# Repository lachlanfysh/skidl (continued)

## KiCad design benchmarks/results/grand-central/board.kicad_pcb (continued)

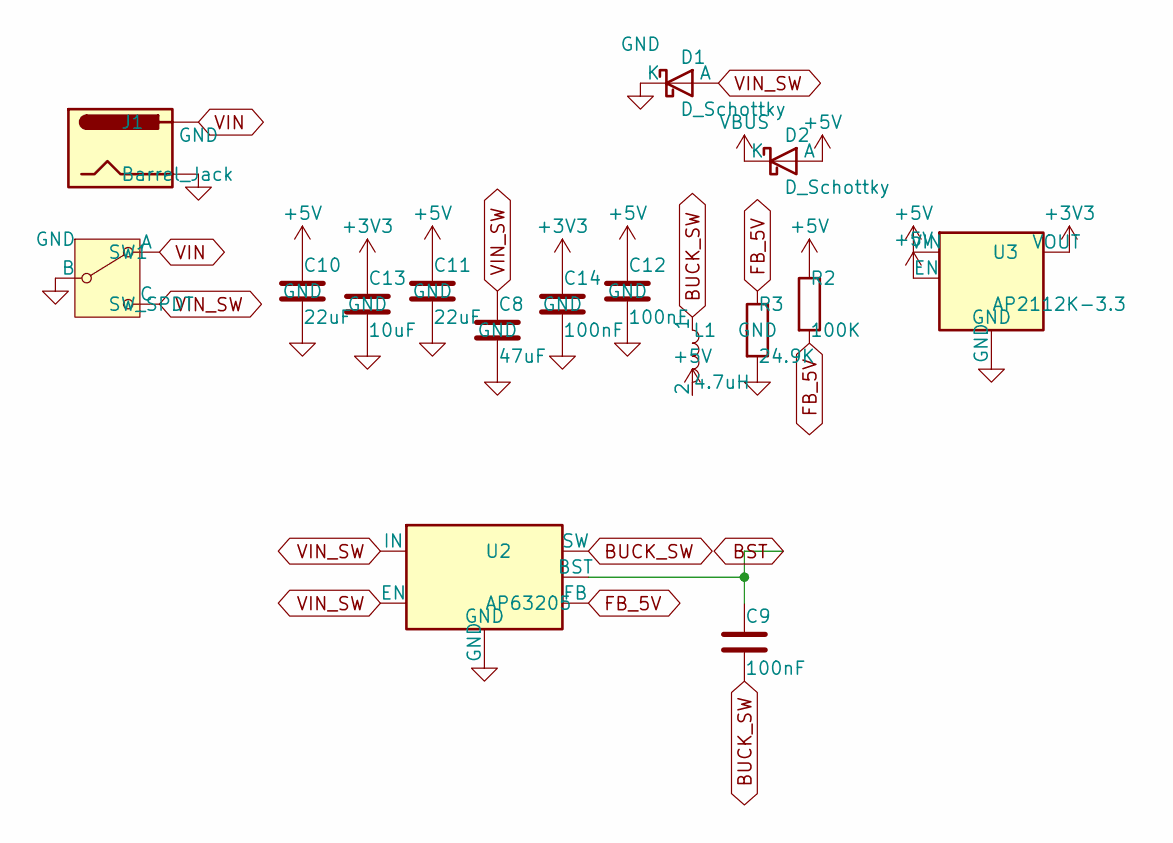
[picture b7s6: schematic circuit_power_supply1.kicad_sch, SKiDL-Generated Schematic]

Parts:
C8: 47uF; C_0805_2012Metric
C9, C12, C14: 100nF; C_0603_1608Metric
C10, C11: 22uF; C_0805_2012Metric
C13: 10uF; C_0805_2012Metric
D1, D2: D_Schottky; D_SMA
J1: Barrel_Jack; BarrelJack_CUI_PJ-063AH_Horizontal
L1: 4.7uH; L_0805_2012Metric
R2: 100K; R_0603_1608Metric
R3: 24.9K; R_0603_1608Metric
SW1: SW_SPDT; SW_DIP_SPSTx01_Slide_6.7x4.1mm_W8.61mm_P2.54mm_LowProfile
U2: AP63205; SOT-23-6
U3: AP2112K-3.3; SOT-23-5

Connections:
+3V3: C13.1, C14.1, U3.5 (VOUT); also elsewhere on the board
+5V: C10.1, C11.1, C12.1, D2.2 (A), L1.2, R2.1, U3.1 (VIN), U3.3 (EN); also elsewhere on the board
BST: C9.1, U2.6 (BST)
BUCK_SW: C9.2, L1.1, U2.5 (SW)
FB_5V: R2.2, R3.1, U2.1 (FB)
GND: C8.2, C10.2, C11.2, C12.2, C13.2, C14.2, D1.1 (K), J1.2, R3.2, SW1.2 (B), U2.4 (GND), U3.2 (GND); also elsewhere on the board
VBUS: D2.1 (K); also elsewhere on the board
VIN: J1.1, SW1.1 (A); also elsewhere on the board
VIN_SW: C8.1, D1.2 (A), SW1.3 (C), U2.2 (EN), U2.3 (IN)

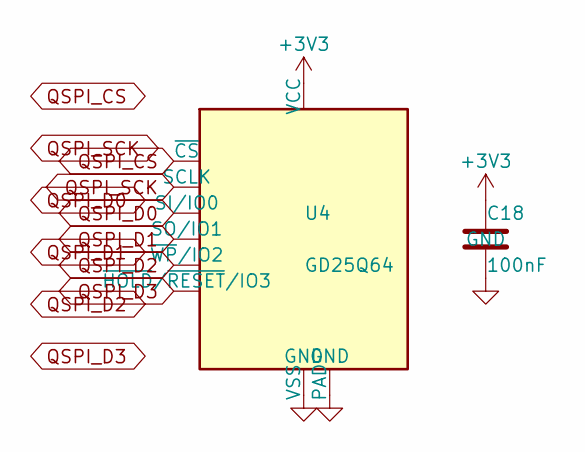
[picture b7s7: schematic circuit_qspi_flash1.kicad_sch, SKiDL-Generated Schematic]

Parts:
C18: 100nF; C_0603_1608Metric
U4: GD25Q64; SOIC-8_3.9x4.9mm_P1.27mm

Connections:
+3V3: C18.1, U4.8 (VCC); also elsewhere on the board
GND: C18.2, U4.4 (VSS), U4.9 (PAD); also elsewhere on the board
QSPI_CS: U4.1 (~CS); also elsewhere on the board
QSPI_D0: U4.5 (SI/IO0); also elsewhere on the board
QSPI_D1: U4.2 (SO/IO1); also elsewhere on the board
QSPI_D2: U4.3 (~WP/IO2); also elsewhere on the board
QSPI_D3: U4.7 (~HOLD/~RESET/IO3); also elsewhere on the board
QSPI_SCK: U4.6 (SCLK); also elsewhere on the board

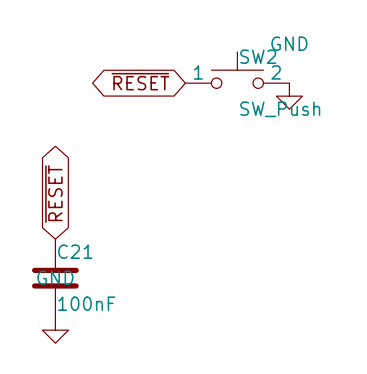
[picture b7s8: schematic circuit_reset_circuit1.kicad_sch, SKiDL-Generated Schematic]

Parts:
C21: 100nF; C_0603_1608Metric
SW2: SW_Push; SW_DIP_SPSTx01_Slide_6.7x4.1mm_W8.61mm_P2.54mm_LowProfile

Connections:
GND: C21.2, SW2.2; also elsewhere on the board
~RESET: C21.1, SW2.1; also elsewhere on the board

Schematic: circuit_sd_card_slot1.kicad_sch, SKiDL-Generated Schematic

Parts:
C19: 100nF; C_0603_1608Metric
J3: Micro_SD_Card; microSD_HC_Hirose_DM3AT-SF-PEJM5
R4, R5: 10K; R_0603_1608Metric

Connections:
+3V3: C19.1, J3.4 (VDD), R4.1, R5.1; also elsewhere on the board
GND: C19.2, J3.6 (VSS), J3.9 (SHIELD); also elsewhere on the board
SD_CS: J3.2 (DAT3/CD); also elsewhere on the board
SD_DAT1: J3.8 (DAT1), R4.2
SD_DAT2: J3.1 (DAT2), R5.2
SD_MISO: J3.7 (DAT0); also elsewhere on the board
SD_MOSI: J3.3 (CMD); also elsewhere on the board
SD_SCK: J3.5 (CLK); also elsewhere on the board

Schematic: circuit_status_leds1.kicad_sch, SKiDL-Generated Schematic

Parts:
D5, D6: LED; LED_0603_1608Metric
R6, R7: 1K; R_0603_1608Metric

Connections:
+3V3: D5.1 (K); also elsewhere on the board
GND: R6.2, R7.2; also elsewhere on the board
GPIO13: D6.1 (K); also elsewhere on the board
unnamed: D5.2 (A), R6.1
unnamed: D6.2 (A), R7.1

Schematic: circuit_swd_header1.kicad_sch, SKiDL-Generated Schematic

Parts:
J4: Conn_02x05_Odd_Even; PinHeader_2x05_P1.27mm_Vertical

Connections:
+3V3: J4.1; also elsewhere on the board
GND: J4.3, J4.5, J4.6, J4.7, J4.8, J4.9; also elsewhere on the board
SWDCLK: J4.4; also elsewhere on the board
SWDIO: J4.2; also elsewhere on the board
~RESET: J4.10; also elsewhere on the board

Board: 2 copper layers, 53 parts (0 on the bottom side), 63 nets, no tracks yet.

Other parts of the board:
C15: 100nF; C_0603_1608Metric
D3: D_TVS; D_SMA
J2: USB_B_Micro; USB_Micro-B_Molex-105017-0001

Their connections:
GND: C15.2, D3.2, J2.5, J2.6; also elsewhere on the board
USB_DM: J2.2; also elsewhere on the board
USB_DP: D3.1, J2.3; also elsewhere on the board
VBUS: C15.1, J2.1; also elsewhere on the board

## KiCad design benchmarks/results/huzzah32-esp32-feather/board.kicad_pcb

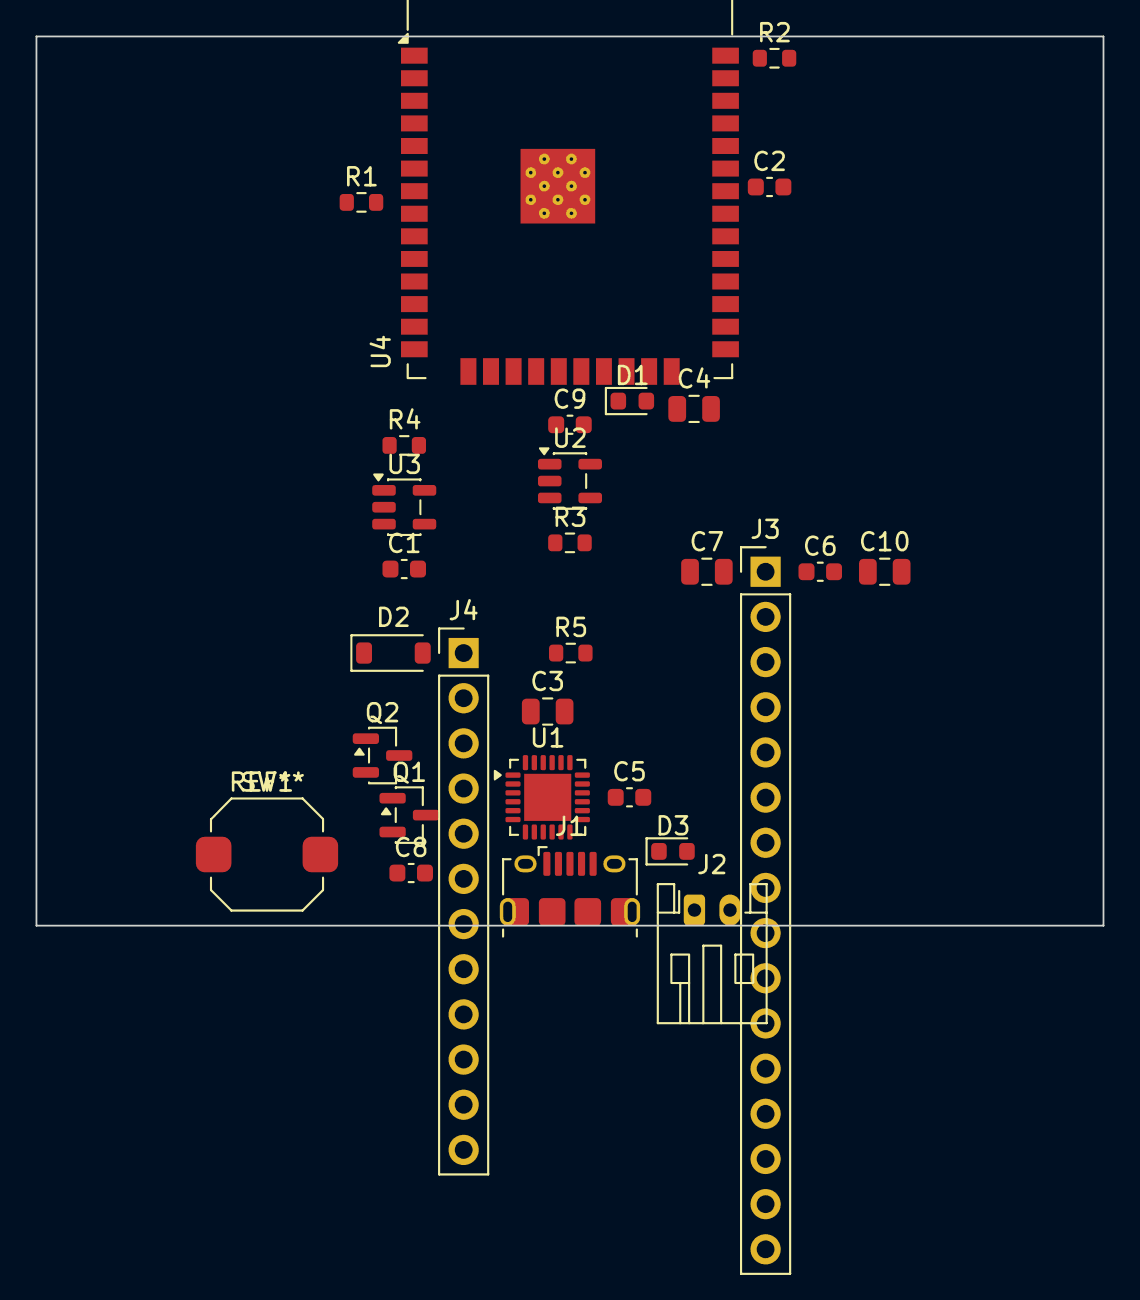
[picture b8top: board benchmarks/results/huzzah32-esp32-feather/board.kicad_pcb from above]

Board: 2 copper layers, 60.0 x 50.0 mm, 29 parts (0 on the bottom side), 35 nets, no tracks yet.

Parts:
C1, C2, C5, C6, C8, C9: 100nF; C_0603_1608Metric
C3, C4: 4.7uF; C_0805_2012Metric
C7, C10: 10uF; C_0805_2012Metric
D1: ORANGE; LED_0603_1608Metric
D2: MBR120; D_SOD-123
D3: RED; LED_0603_1608Metric
J1: USB_B_Micro; USB_Micro-B_Amphenol_10118194_Horizontal
J2: Conn_01x02; JST_PH_S2B-PH-K_1x02_P2.00mm_Horizontal
J3: Conn_01x16; PinHeader_1x16_P2.54mm_Vertical
J4: Conn_01x12; PinHeader_1x12_P2.54mm_Vertical
Q1, Q2: Q_NPN; SOT-23
R1, R2: 10K; R_0603_1608Metric
R3: 2K; R_0603_1608Metric
R4, R5: 1K; R_0603_1608Metric
SW1: SW_Push; SW_Push_1TS009xxxx-xxxx-xxxx_6x6x5mm
U1: CP2104; QFN-24-1EP_4x4mm_P0.5mm_EP2.65x2.65mm
U2: MCP73831-2-OT; SOT-23-5
U3: AP2112K-3.3; SOT-23-5
U4: ESP32-WROOM-32

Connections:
+3V3: C2.1, C6.1, C7.1, C9.1, C10.1, J3.2, R1.1, R2.1, U1.5, U3.5, U4.2
CHG_STAT: D1.1, U2.1
EN: C8.1, J3.1, J4.2, R1.2, SW1.1, U4.3
GND: C1.2, C2.2, C3.2, C4.2, C5.2, C6.2, C7.2, C8.2, C9.2, C10.2, D3.1, J1.5, J1.6, J2.2, J3.4, R3.2, SW1.2, U1.2, U1.25, U2.2, U3.2, U4.1, U4.15, U4.38, U4.39
IO0: R2.2, U4.25
IO4: J3.10, U4.26
IO5: J3.11, U4.29
IO12: J4.5, U4.14
IO13: J4.4, R5.1, U4.16
IO14: J4.10, U4.13
IO15: J4.8, U4.23
IO16: J3.14, U4.27
IO17: J3.15, U4.28
IO18: J3.12, U4.30
IO19: J3.13, U4.31
IO21: J3.16, U4.33
IO22: J4.11, U4.36
IO23: J4.12, U4.37
IO25: J3.6, U4.10
IO26: J3.5, U4.11
IO27: J4.6, U4.12
IO32: J4.9, U4.8
IO33: J4.7, U4.9
IO34: J3.7, U4.6
unnamed: D1.2, R4.2
unnamed: D3.2, R5.2
PROG: R3.1, U2.5
RXD0: U1.21, U4.34
SENSOR_VN: J3.8, U4.5
SENSOR_VP: J3.9, U4.4
TXD0: U1.20, U4.35
USB_D+: J1.3, U1.3
USB_D-: J1.2, U1.4
VBAT: C4.1, D2.2, J2.1, J4.1, U2.3
VBUS: C1.1, C3.1, C5.1, D2.1, J1.1, J4.3, R4.1, U1.6, U1.7, U2.4, U3.1, U3.3

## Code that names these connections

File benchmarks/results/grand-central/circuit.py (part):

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              qspi_sck, qspi_cs, qspi_d0, qspi_d1, qspi_d2, qspi_d3,
              sd_sck, sd_mosi, sd_miso, sd_cs,
              neopixel_data, i2s_sck, i2s_ws, i2s_sd,
              swdio, swdclk, aref, dac0_out, dac1_out, vddcore, gpio):
    """ATSAMD51J20A in 64-pin TQFP with decoupling and crystals."""

    mcu = Part("MCU_Microchip_SAMD", "ATSAMD51J20A-A", value="ATSAMD51J20A",
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    c_vcore[1] += vddcore
    c_vcore[2] += gnd

    # USB (PA24=D-, PA25=D+)
    mcu["PA24"] += usb_dm
    mcu["PA25"] += usb_dp

    # Reset with pull-up
    mcu["~{RESET}"] += reset_n
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    r_rst[1] += v3v3
    r_rst[2] += reset_n

    # SWD (PA30=SWCLK, PA31=SWDIO)
    mcu["PA30"] += swdclk
    mcu["PA31"] += swdio

    # AREF (VDDANA pin provides analog reference, PA03 is VREFA)
    mcu["PA03"] += aref

    # QSPI flash connections (PA08-PA11 = D0-D3, PB10=SCK, PB11=CS)
    mcu["PA08"] += qspi_d0
    mcu["PA09"] += qspi_d1
    mcu["PA10"] += qspi_d2
    mcu["PA11"] += qspi_d3
    mcu["PB10"] += qspi_sck
    mcu["PB11"] += qspi_cs

    # SD card SPI (using SERCOM on PB12-PB15)
    mcu["PB12"] += sd_mosi
    mcu["PB13"] += sd_sck
    mcu["PB14"] += sd_miso
    mcu["PB15"] += sd_cs

    # NeoPixel (PB22)
    mcu["PB22"] += neopixel_data

    # I2S (PB16=SCK, PB17=WS, PA22=SD)
    mcu["PB16"] += i2s_sck
    mcu["PB17"] += i2s_ws
    mcu["PA22"] += i2s_sd

    # DAC outputs (PA02=DAC0, PA05=DAC1)
    mcu["PA02"] += dac0_out
    mcu["PA05"] += dac1_out

    # GPIO pin assignments to headers
    gpio_map = {
        "PA00": 0, "PA01": 1,
        "PA04": 2, "PA06": 3, "PA07": 4,
        "PA12": 5, "PA13": 6, "PA14": 7, "PA15": 8,
        "PA16": 9, "PA17": 10, "PA18": 11, "PA19": 12,
        "PA20": 13, "PA21": 14, "PA23": 15, "PA27": 16,
        "PB00": 17, "PB01": 18, "PB02": 19, "PB03": 20,
        "PB04": 21, "PB05": 22, "PB06": 23, "PB07": 24,
        "PB08": 25, "PB09": 26,
        "PB23": 27, "PB30": 28, "PB31": 29,
    }
    for pin_name, gpio_idx in gpio_map.items():
        mcu[pin_name] += gpio[gpio_idx]
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@subcircuit
def crystal_oscillators(v3v3, gnd, gpio):
    """12MHz main crystal and 32.768kHz RTC crystal.
    Connected to PA00/PA01 (XIN/XOUT) for main and PB**/PB** for 32k."""

    # Note: SAMD51 J variant has no dedicated XOSC pins.
    # Main clock typically uses internal DFLL48M with USB SOF reference.
    # 32.768kHz crystal on PA00 (XIN32) / PA01 (XOUT32) for RTC.
    y_rtc = Part("Device", "Crystal", value="32.768kHz",
                 footprint="Crystal:Crystal_SMD_2012-2Pin_2.0x1.2mm")
    xin32 = gpio[0]    # PA00 = XIN32
    xout32 = gpio[1]   # PA01 = XOUT32
    y_rtc[1] += xin32
    y_rtc[2] += xout32

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    j_swd[1] += v3v3       # Pin 1: VTref
    j_swd[2] += swdio      # Pin 2: SWDIO
    j_swd[3] += gnd        # Pin 3: GND
    j_swd[4] += swdclk     # Pin 4: SWDCLK
    j_swd[5] += gnd        # Pin 5: GND
    j_swd[6] += gnd
    j_swd[7] += gnd
    j_swd[8] += gnd
    j_swd[9] += gnd
    j_swd[10] += reset_n   # Pin 10: nRESET


# ============================================================
# Subcircuit: Arduino Headers
# ============================================================
@subcircuit
def arduino_headers(v5v, v3v3, gnd, gpio, aref, dac0_out, dac1_out, reset_n, vin_raw):
    """Arduino Mega form factor pin headers."""

    # Digital header 1 (1x16): D0-D13, GND, AREF
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    # ICSP/SPI header (2x3)
    j_icsp = Part("Connector_Generic", "Conn_02x03_Odd_Even",
                  footprint="Connector_PinHeader_2.54mm:PinHeader_2x03_P2.54mm_Vertical")
    j_icsp[1] += gpio[26]   # MISO (PB09)
    j_icsp[2] += v5v
    j_icsp[3] += gpio[25]   # SCK (PB08)
    j_icsp[4] += gpio[24]   # MOSI (PB07)
    j_icsp[5] += reset_n
    j_icsp[6] += gnd

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# ============================================================
@subcircuit
def status_leds(v3v3, gnd, gpio):
    """Power LED + user LED (on GPIO13 / D13)."""

    # Power LED (green)
    led_pwr = Part("Device", "LED",
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          qspi_sck, qspi_cs, qspi_d0, qspi_d1, qspi_d2, qspi_d3,
          sd_sck, sd_mosi, sd_miso, sd_cs,
          neopixel_data, i2s_sck, i2s_ws, i2s_sd,
          swdio, swdclk, aref, dac0_out, dac1_out, vddcore, gpio)

power_supply(vin_raw, vin_switched, v5v, v3v3, vbus, gnd)

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
swd_header(v3v3, gnd, swdio, swdclk, reset_n)

arduino_headers(v5v, v3v3, gnd, gpio, aref, dac0_out, dac1_out, reset_n, vin_raw)

status_leds(v3v3, gnd, gpio)

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
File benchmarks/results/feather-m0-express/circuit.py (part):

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ATSAMD21G18A ARM Cortex M0+ 48MHz, 3.3V.
256KB flash, 32KB RAM. USB bootloader (UF2).
2MB SPI flash (GD25Q16) for CircuitPython.
NeoPixel WS2812B on PA06. MCP73831 LiPo charger.
AP2112K-3.3 LDO. Schottky diode USB/battery OR.
Feather form factor ~51x23mm, 2x 1x16 + 1x12 headers.
"""
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                 footprint="Capacitor_SMD:C_0603_1608Metric", ref="C_MCU" + str(i+1))
        v3v3 += c[1]; gnd += c[2]

    # USB D+/D- (PA24=D-, PA25=D+)
    mcu["PA24"] += usb_dm
    mcu["PA25"] += usb_dp

    # 32.768kHz crystal PA00/PA01
    mcu["PA00"] += xin
    mcu["PA01"] += xout

    # Reset (pin 40 = ~{RESET} — use pin number for reliability)
    mcu[40] += reset_n

    # SWD: PA30=SWCLK, PA31=SWDIO
    mcu["PA30"] += swclk
    mcu["PA31"] += swdio

    # I2C SERCOM3: PA22=SDA, PA23=SCL
    mcu["PA22"] += sda
    mcu["PA23"] += scl

    # SPI (flash+header) SERCOM4: PB10=MOSI, PA12=MISO, PB11=SCK
    mcu["PB10"] += mosi
    mcu["PA12"] += miso
    mcu["PB11"] += sck
    mcu["PA13"] += flash_cs

    # NeoPixel data PA06
    mcu["PA06"] += neo_data

    # Battery divider ADC PA07
    mcu["PA07"] += bat_div

    # Analog header
    mcu["PA02"] += a0
    mcu["PB08"] += a1
    mcu["PB09"] += a2
    mcu["PA04"] += a3
    mcu["PA05"] += a4
    mcu["PB02"] += a5

    # Digital header
    mcu["PA17"] += d13   # D13/SCK
    mcu["PA19"] += d12   # D12/MISO
    mcu["PA16"] += d11   # D11/MOSI
    mcu["PA18"] += d10
    mcu["PA20"] += d9
    mcu["PA15"] += d6
    mcu["PA14"] += d5

    # UART SERCOM0
    mcu["PA10"] += tx
    mcu["PA11"] += rx

    # I2C pull-ups
    rsda = Part("Device", "R", value="4.7k",
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    v3v3 += rsda[1]; rsda[2] += sda
    v3v3 += rscl[1]; rscl[2] += scl

    # PA03 = VREFA, connect to 3V3 as analog reference
    mcu["PA03"] += v3v3

    # Unused pads to GND
    for pin in ["PA08", "PA09", "PA21", "PA27", "PA28",
                "PB03", "PB22", "PB23"]:
        mcu[pin] += gnd


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
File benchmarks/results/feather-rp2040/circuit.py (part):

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    # TESTEN — tie to ground (pin 19)
    mcu[19] += gnd  # TESTEN

    # DVDD decoupling (per RP2040 datasheet: 100nF per DVDD pin)
    c_dvdd1 = Part("Device", "C", value="100nF",
                   footprint="Capacitor_SMD:C_0402_1005Metric")
    c_dvdd1[1] += dvdd
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    c_bulk[1] += v3v3
    c_bulk[2] += gnd

    # ── USB (pin 46=USB_DM, pin 47=USB_DP) ──────────────
    # RP2040 has internal USB series resistors — direct connection
    mcu[46] += usb_dm   # USB_DM
    mcu[47] += usb_dp   # USB_DP

    # ── 12MHz Crystal (pin 20=XIN, pin 21=XOUT) ─────────
    xin_net  = Net("XIN")
    xout_net = Net("XOUT")
    mcu[20] += xin_net   # XIN
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    sw_rst[1] += reset_n
    sw_rst[2] += gnd

    # Bootloader button (BOOTSEL — GPIO via 1-wire on Feather RP2040)
    boot_net = Net("BOOTSEL")
    sw_boot = Part("Switch", "SW_Push",
                   footprint="Button_Switch_SMD:SW_Push_1P1T_NO_CK_KMR2",
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    mcu[56] += qspi_ss     # ~QSPI_SS

    # GPIO pin number map (from RP2040 datasheet):
    # pin 2=GPIO0, 3=GPIO1, 4=GPIO2, 5=GPIO3, 6=GPIO4, 7=GPIO5,
    # 8=GPIO6, 9=GPIO7, 11=GPIO8, 12=GPIO9, 13=GPIO10, 14=GPIO11,
    # 15=GPIO12, 16=GPIO13, 17=GPIO14, 18=GPIO15, 27=GPIO16, 28=GPIO17,
    # 29=GPIO18, 30=GPIO19, 31=GPIO20, 32=GPIO21, 34=GPIO22, 35=GPIO23,
    # 36=GPIO24, 37=GPIO25, 38=GPIO26/ADC0, 39=GPIO27/ADC1,
    # 40=GPIO28/ADC2, 41=GPIO29/ADC3

    # ── NeoPixel (GPIO16 = pin 27) ────────────────────────────────
    mcu[27] += neopixel

    # ── I2C (GPIO2=pin 4=SDA, GPIO3=pin 5=SCL) ──────────────────
    mcu[4] += sda    # GPIO2/SDA
    mcu[5] += scl    # GPIO3/SCL

    # ── UART (GPIO0=pin 2=TX, GPIO1=pin 3=RX) ───────────────────
    mcu[2] += uart_tx   # GPIO0/TX
    mcu[3] += uart_rx   # GPIO1/RX

    # ── SPI (GPIO18=pin 29=SCK, GPIO19=pin 30=MOSI, GPIO20=pin 31=MISO)
    mcu[29] += spi_sck    # GPIO18/SCK
    mcu[30] += spi_mosi   # GPIO19/MOSI
    mcu[31] += spi_miso   # GPIO20/MISO

    # ── Analog Inputs ────────────────────────────────────
    mcu[38] += a0    # GPIO26/ADC0
    mcu[39] += a1    # GPIO27/ADC1
    mcu[40] += a2    # GPIO28/ADC2
    mcu[41] += a3    # GPIO29/ADC3

    # ── Digital I/O ──────────────────────────────────────
    mcu[6]  += d4    # GPIO4
    mcu[7]  += d5    # GPIO5
    mcu[8]  += d6    # GPIO6
    mcu[9]  += d9    # GPIO7 → D9
    mcu[11] += d10   # GPIO8 → D10
    mcu[12] += d11   # GPIO9 → D11
    mcu[13] += d12   # GPIO10 → D12
    mcu[14] += d13   # GPIO11 → D13
    mcu[36] += d24   # GPIO24
    mcu[37] += d25   # GPIO25

    # ── User LED (D13 / GPIO11, active-high) ─────────────
    led_d13 = Part("Device", "LED", value="Red",
                   footprint="LED_SMD:LED_0603_1608Metric")
    r_d13 = Part("Device", "R", value="1K",
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    led_d13["K"] += gnd          # Cathode to GND

    # ── Unused GPIOs (by pin number) ──────────────────────
    mcu[15] += NC   # GPIO12
    mcu[16] += NC   # GPIO13
    mcu[17] += NC   # GPIO14
    mcu[18] += NC   # GPIO15
    mcu[28] += NC   # GPIO17
    mcu[32] += NC   # GPIO21
    mcu[34] += NC   # GPIO22
    mcu[35] += NC   # GPIO23


mcu_rp2040(v3v3, gnd, usb_dp, usb_dm, reset_n, swdio, swdclk,
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
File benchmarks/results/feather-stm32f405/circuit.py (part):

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    c_bulk[2] += gnd

    # ── USB ──────────────────────────────────────────────
    mcu["PA11"] += usb_dm   # USB OTG FS D-
    mcu["PA12"] += usb_dp   # USB OTG FS D+

    # ── Reset ────────────────────────────────────────────
    mcu["NRST"] += reset_n
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    r_boot[2] += gnd

    # ── SWD Debug ────────────────────────────────────────
    mcu["PA13"] += swdio    # SWDIO
    mcu["PA14"] += swdclk   # SWCLK

    # ── 8MHz HSE Crystal ─────────────────────────────────
    hse_in  = Net("HSE_IN")
    hse_out = Net("HSE_OUT")
    mcu["PH0"] += hse_in    # OSC_IN
    mcu["PH1"] += hse_out   # OSC_OUT

    xtal_hse = Part("Device", "Crystal", value="8MHz",
                    footprint="Crystal:Crystal_SMD_3225-4Pin_3.2x2.5mm")
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    # ── 32.768kHz LSE Crystal ────────────────────────────
    lse_in  = Net("LSE_IN")
    lse_out = Net("LSE_OUT")
    mcu["PC14"] += lse_in    # OSC32_IN
    mcu["PC15"] += lse_out   # OSC32_OUT

    xtal_lse = Part("Device", "Crystal", value="32.768kHz",
                    footprint="Crystal:Crystal_SMD_3215-2Pin_3.2x1.5mm")
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    c_lse2[2] += gnd

    # ── SPI Flash (QSPI bus) ────────────────────────────
    mcu["PB3"]  += spi_sck    # SPI1_SCK
    mcu["PB4"]  += spi_miso   # SPI1_MISO
    mcu["PB5"]  += spi_mosi   # SPI1_MOSI
    mcu["PA15"] += flash_cs   # SPI flash CS

    # ── SD Card (SPI mode on SPI2) ───────────────────────
    mcu["PB13"] += sd_sck     # SPI2_SCK
    mcu["PB14"] += sd_miso    # SPI2_MISO
    mcu["PB15"] += sd_mosi    # SPI2_MOSI
    mcu["PB12"] += sd_cs      # SD card CS

    # ── NeoPixel ─────────────────────────────────────────
    mcu["PC0"] += neopixel_data   # NeoPixel data

    # ── I2C ──────────────────────────────────────────────
    mcu["PB6"] += scl     # I2C1_SCL
    mcu["PB7"] += sda     # I2C1_SDA

    # ── UART ─────────────────────────────────────────────
    mcu["PB10"] += uart_tx    # USART3_TX
    mcu["PB11"] += uart_rx    # USART3_RX

    # ── Analog Inputs ────────────────────────────────────
    mcu["PA0"] += a0     # A0 / ADC1_IN0
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    mcu["PA7"]  += NC
    mcu["PA8"]  += NC
    mcu["PA9"]  += NC
    mcu["PA10"] += NC
    mcu["PB0"]  += NC
    mcu["PB2"]  += NC
    mcu["PC4"]  += NC
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    sd = Part("Connector", "Micro_SD_Card",
              footprint="Connector_Card:microSD_HC_Molex_104031-0811",
              value="MicroSD")
    sd["CLK"]     += sd_sck      # Pin 5
    sd["CMD"]     += sd_mosi     # Pin 3 (MOSI in SPI mode)
    sd["DAT0"]    += sd_miso     # Pin 7 (MISO in SPI mode)
    sd["DAT3/CD"] += sd_cs       # Pin 2 (CS in SPI mode)
    sd["VDD"]     += v3v3        # Pin 4
    sd["VSS"]     += gnd         # Pin 6
    sd["DAT1"]    += NC          # Not used in SPI mode
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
